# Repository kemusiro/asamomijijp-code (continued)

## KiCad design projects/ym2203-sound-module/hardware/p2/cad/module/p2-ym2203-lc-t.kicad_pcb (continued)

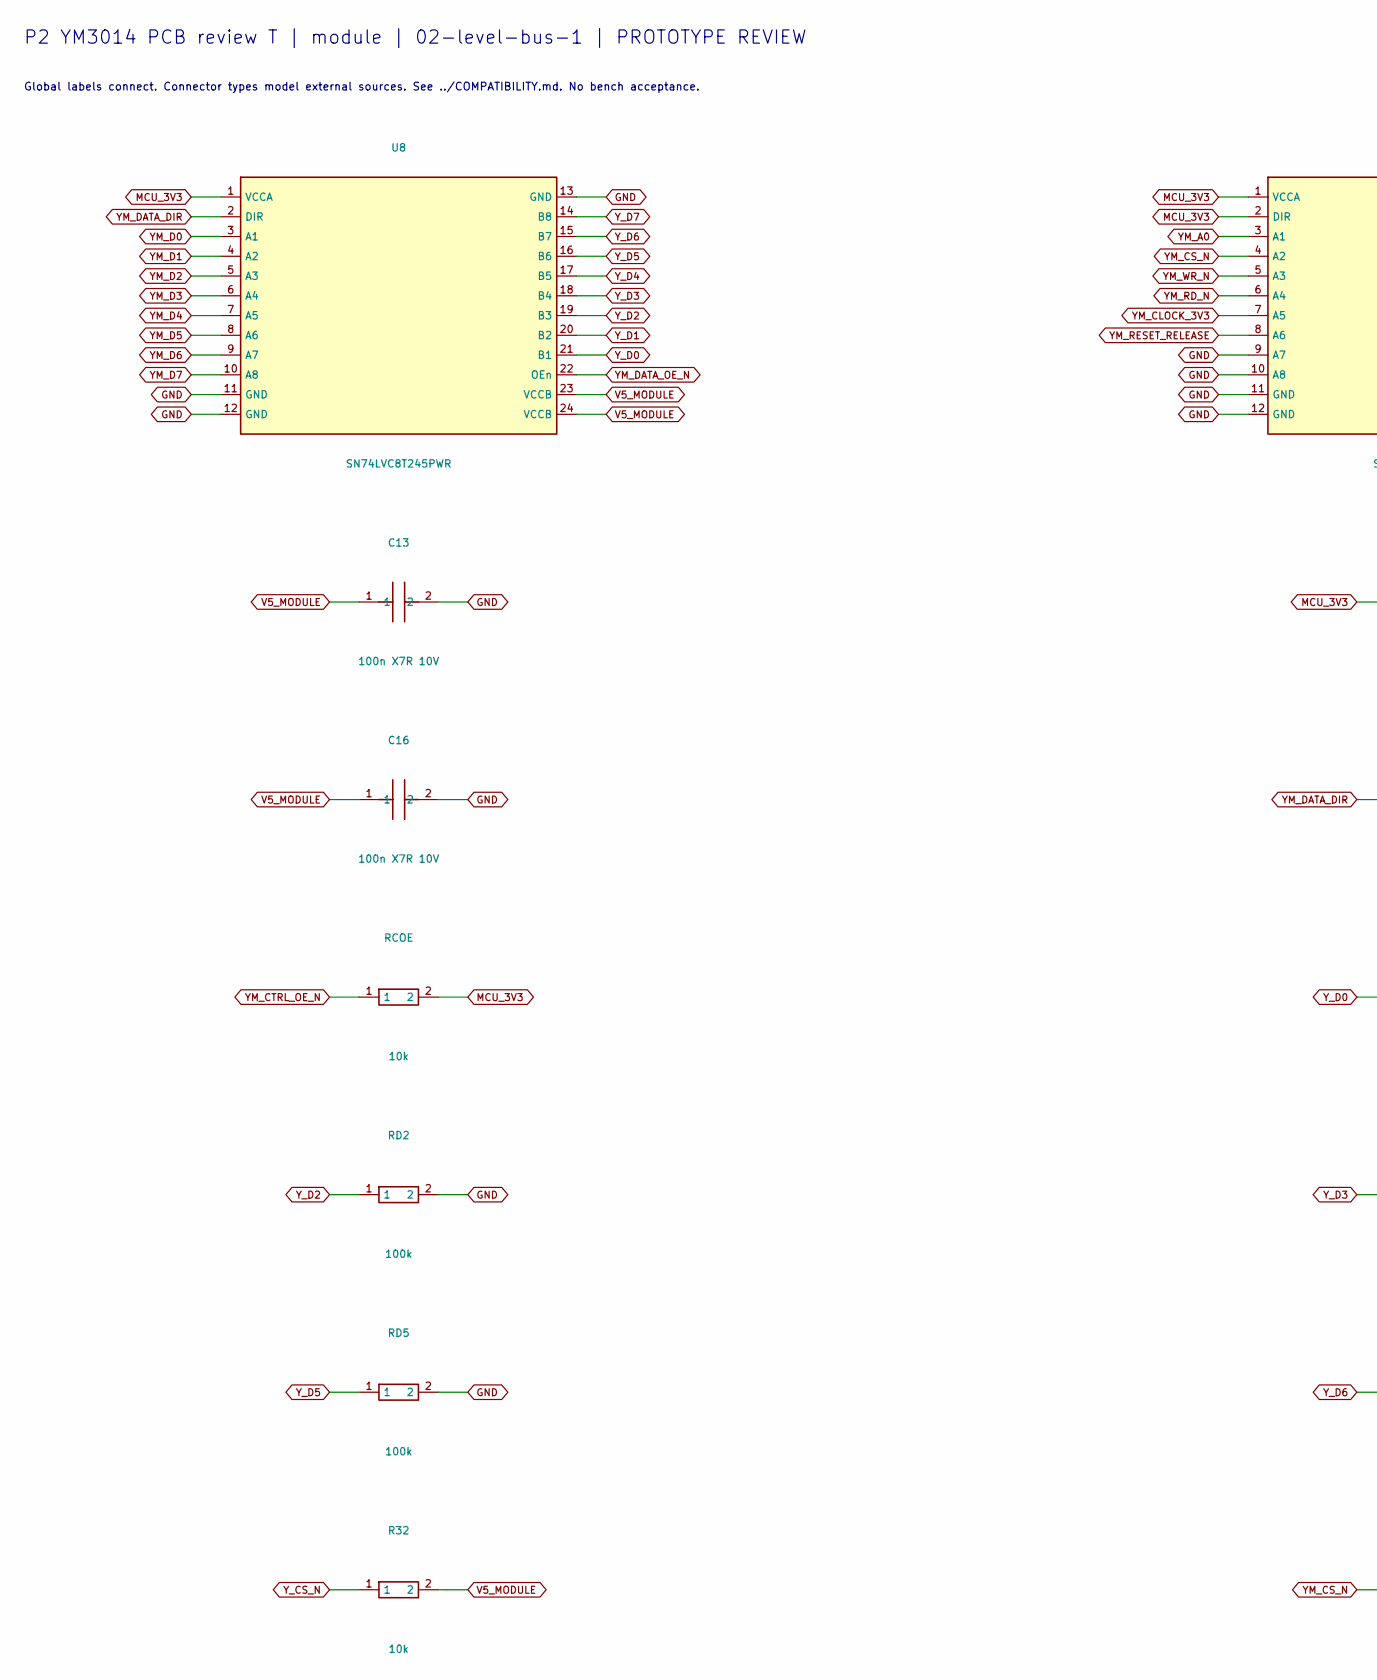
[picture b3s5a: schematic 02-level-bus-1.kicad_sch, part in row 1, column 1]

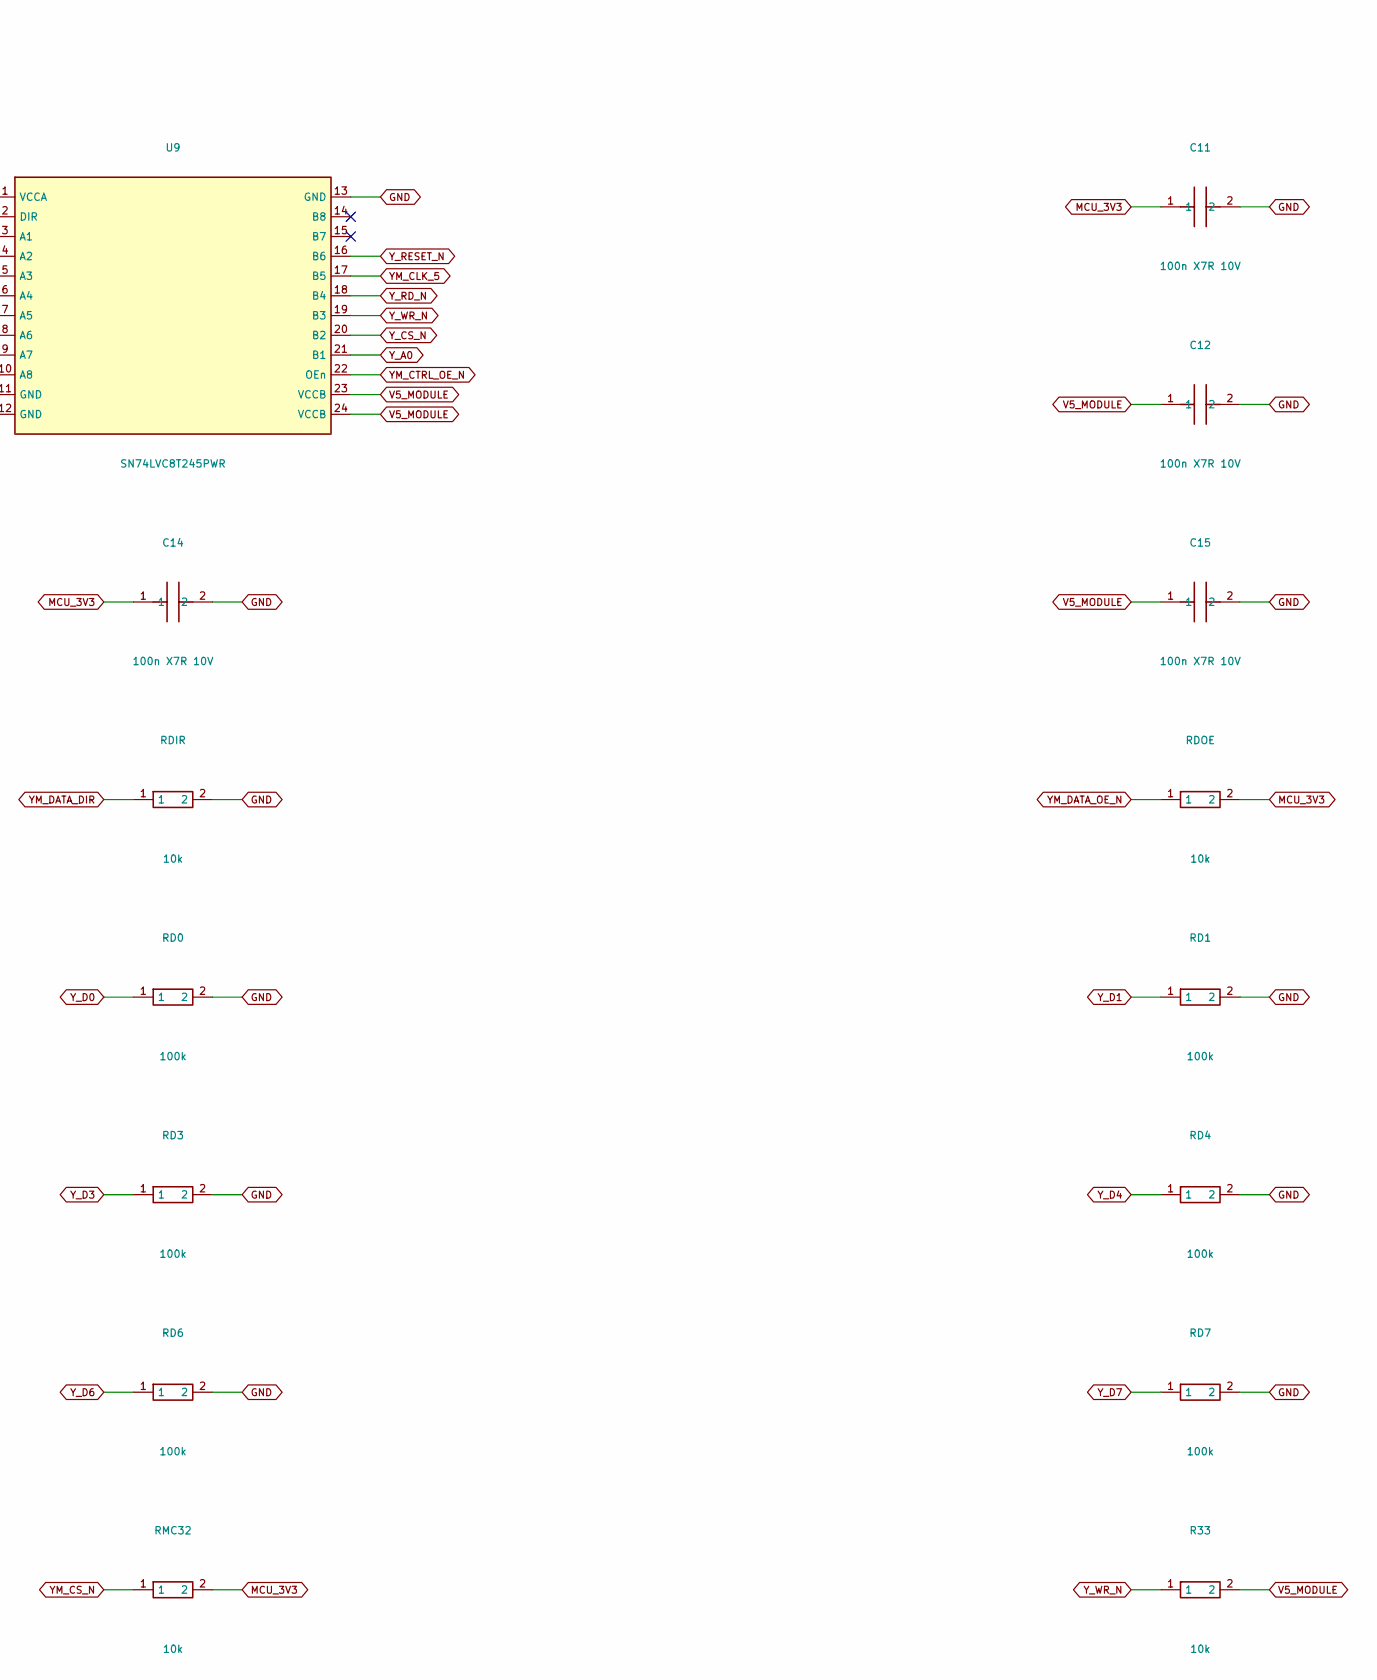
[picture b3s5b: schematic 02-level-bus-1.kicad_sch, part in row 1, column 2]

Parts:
C11, C12, C13, C14, C15, C16: 100n X7R 10V; C_0805_2012Metric
R32, R33: 10k; R_0805_2012Metric
RCOE: 10k; R_0805_2012Metric
RD0, RD1, RD2, RD3, RD4, RD5, RD6, RD7: 100k; R_0805_2012Metric
RDIR: 10k; R_0805_2012Metric
RDOE: 10k; R_0805_2012Metric
RMC32: 10k; R_0805_2012Metric
U8, U9: SN74LVC8T245PWR; TSSOP-24_4.4x7.8mm_P0.65mm

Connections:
GND: C11.2, C12.2, C13.2, C14.2, C15.2, C16.2, RD0.2, RD1.2, RD2.2, RD3.2, RD4.2, RD5.2, RD6.2, RD7.2, RDIR.2, U8.11 (GND), U8.12 (GND), U8.13 (GND), U9.9 (A7), U9.10 (A8), U9.11 (GND), U9.12 (GND), U9.13 (GND); also elsewhere on the board
MCU_3V3: C11.1, C14.1, RCOE.2, RDOE.2, RMC32.2, U8.1 (VCCA), U9.1 (VCCA), U9.2 (DIR); also elsewhere on the board
V5_MODULE: C12.1, C13.1, C15.1, C16.1, R32.2, R33.2, U8.23 (VCCB), U8.24 (VCCB), U9.23 (VCCB), U9.24 (VCCB); also elsewhere on the board
YM_A0: U9.3 (A1); also elsewhere on the board
YM_CLK_5: U9.17 (B5); also elsewhere on the board
YM_CLOCK_3V3: U9.7 (A5); also elsewhere on the board
YM_CS_N: RMC32.1, U9.4 (A2); also elsewhere on the board
YM_CTRL_OE_N: RCOE.1, U9.22 (OEn); also elsewhere on the board
YM_D0: U8.3 (A1); also elsewhere on the board
YM_D1: U8.4 (A2); also elsewhere on the board
YM_D2: U8.5 (A3); also elsewhere on the board
YM_D3: U8.6 (A4); also elsewhere on the board
YM_D4: U8.7 (A5); also elsewhere on the board
YM_D5: U8.8 (A6); also elsewhere on the board
YM_D6: U8.9 (A7); also elsewhere on the board
YM_D7: U8.10 (A8); also elsewhere on the board
YM_DATA_DIR: RDIR.1, U8.2 (DIR); also elsewhere on the board
YM_DATA_OE_N: RDOE.1, U8.22 (OEn); also elsewhere on the board
YM_RD_N: U9.6 (A4); also elsewhere on the board
YM_RESET_RELEASE: U9.8 (A6); also elsewhere on the board
YM_WR_N: U9.5 (A3); also elsewhere on the board
Y_A0: U9.21 (B1); also elsewhere on the board
Y_CS_N: R32.1, U9.20 (B2); also elsewhere on the board
Y_D0: RD0.1, U8.21 (B1); also elsewhere on the board
Y_D1: RD1.1, U8.20 (B2); also elsewhere on the board
Y_D2: RD2.1, U8.19 (B3); also elsewhere on the board
Y_D3: RD3.1, U8.18 (B4); also elsewhere on the board
Y_D4: RD4.1, U8.17 (B5); also elsewhere on the board
Y_D5: RD5.1, U8.16 (B6); also elsewhere on the board
Y_D6: RD6.1, U8.15 (B7); also elsewhere on the board
Y_D7: RD7.1, U8.14 (B8); also elsewhere on the board
Y_RD_N: U9.18 (B4); also elsewhere on the board
Y_RESET_N: U9.16 (B6); also elsewhere on the board
Y_WR_N: R33.1, U9.19 (B3); also elsewhere on the board

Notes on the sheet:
P2 YM3014 PCB review T | module | 02-level-bus-1 | PROTOTYPE REVIEW
Global labels connect. Connector types model external sources. See ../COMPATIBILITY.md. No bench acceptance.

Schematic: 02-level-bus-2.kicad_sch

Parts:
R34: 10k; R_0805_2012Metric
R35: 100k; R_0805_2012Metric
RMA: 100k; R_0805_2012Metric
RMC33, RMC34: 10k; R_0805_2012Metric

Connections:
GND: R35.2, RMA.2; also elsewhere on the board
MCU_3V3: RMC33.2, RMC34.2; also elsewhere on the board
V5_MODULE: R34.2; also elsewhere on the board
YM_A0: RMA.1; also elsewhere on the board
YM_RD_N: RMC34.1; also elsewhere on the board
YM_WR_N: RMC33.1; also elsewhere on the board
Y_A0: R35.1; also elsewhere on the board
Y_RD_N: R34.1; also elsewhere on the board

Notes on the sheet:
P2 YM3014 PCB review T | module | 02-level-bus-2 | PROTOTYPE REVIEW
Global labels connect. Connector types model external sources. See ../COMPATIBILITY.md. No bench acceptance.

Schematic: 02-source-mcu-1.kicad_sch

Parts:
DMCU5V: 1N5819; D_DO-41_SOD81_P10.16mm_Horizontal
JSWD: SWD service / program source 2B; PinHeader_1x03_P2.54mm_Vertical
USOURCE: Picossci 2B RP2350B SSCI-105071; Picossci2B_DirectSolder_DebugWire

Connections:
CORE_RUN_N: USOURCE.SW1.S (RESET_EXTRA_WIRE); also elsewhere on the board
CORE_SWCLK: JSWD.1 (SWCLK), USOURCE.JP1.1 (SWCLK)
CORE_SWD: JSWD.3 (SWDIO), USOURCE.JP1.3 (SWDIO)
FM1_LED_N: USOURCE.J2.2 (GP32); also elsewhere on the board
FM2_LED_N: USOURCE.J2.3 (GP33); also elsewhere on the board
FM3_LED_N: USOURCE.J2.4 (GP34); also elsewhere on the board
GND: JSWD.2 (GND), USOURCE.J2.10 (GND), USOURCE.JP1.2 (GND), USOURCE.JP6.8 (GND), USOURCE.JP7.1 (GND); also elsewhere on the board
LINK_TX_DISABLE: USOURCE.JP7.5 (GP27); also elsewhere on the board
MCU_3V3: USOURCE.J1.1 (3V3_OUT), USOURCE.J2.20 (3V3_OUT); also elsewhere on the board
MCU_5V: DMCU5V.1 (K), USOURCE.J2.19 (REG_IN_5V)
MOD_ALERT_DRIVE: USOURCE.JP6.7 (GP23); also elsewhere on the board
MOD_I2S_BCK: USOURCE.JP7.8 (GP30); also elsewhere on the board
MOD_I2S_DATA: USOURCE.JP7.7 (GP29); also elsewhere on the board
MOD_I2S_LRCK: USOURCE.J2.1 (GP31); also elsewhere on the board
MOD_SPI_CS_N: USOURCE.J1.13 (GP9); also elsewhere on the board
MOD_SPI_MISO: USOURCE.J1.15 (GP11); also elsewhere on the board
MOD_SPI_MOSI: USOURCE.J1.12 (GP8); also elsewhere on the board
MOD_SPI_SCK: USOURCE.J1.14 (GP10); also elsewhere on the board
SSGA_LED_N: USOURCE.J2.5 (GP35); also elsewhere on the board
SSGB_LED_N: USOURCE.J2.6 (GP36); also elsewhere on the board
SSGC_LED_N: USOURCE.J2.7 (GP37); also elsewhere on the board
V5_MODULE: DMCU5V.2 (A); also elsewhere on the board
YM_A0: USOURCE.J1.16 (GP12); also elsewhere on the board
YM_CS_N: USOURCE.J1.17 (GP13); also elsewhere on the board
YM_CTRL_OE_N: USOURCE.JP6.5 (GP21); also elsewhere on the board
YM_D0: USOURCE.J1.4 (GP0); also elsewhere on the board
YM_D1: USOURCE.J1.5 (GP1); also elsewhere on the board
YM_D2: USOURCE.J1.6 (GP2); also elsewhere on the board
YM_D3: USOURCE.J1.7 (GP3); also elsewhere on the board
YM_D4: USOURCE.J1.8 (GP4); also elsewhere on the board
YM_D5: USOURCE.J1.9 (GP5); also elsewhere on the board
YM_D6: USOURCE.J1.10 (GP6); also elsewhere on the board
YM_D7: USOURCE.J1.11 (GP7); also elsewhere on the board
YM_DATA_DIR: USOURCE.JP6.3 (GP19); also elsewhere on the board
YM_DATA_OE_N: USOURCE.JP6.4 (GP20); also elsewhere on the board
YM_FM_CLK: USOURCE.JP6.1 (GP17); also elsewhere on the board
YM_FM_SD: USOURCE.J1.20 (GP16); also elsewhere on the board
YM_FM_SH: USOURCE.JP6.2 (GP18); also elsewhere on the board
YM_RD_N: USOURCE.J1.19 (GP15); also elsewhere on the board
YM_RESET_RELEASE: USOURCE.JP6.6 (GP22); also elsewhere on the board
YM_WR_N: USOURCE.J1.18 (GP14); also elsewhere on the board

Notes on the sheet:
P2 YM3014 PCB review T | module | 02-source-mcu-1 | PROTOTYPE REVIEW
Global labels connect. Connector types model external sources. See ../COMPATIBILITY.md. No bench acceptance.

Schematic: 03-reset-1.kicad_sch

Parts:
CURUNOD: 100n X7R 10V; C_0805_2012Metric
RENPD: 10k; R_0805_2012Metric
RRELDEFAULT: 100k; R_0805_2012Metric
RRUNUP: 10k; R_0805_2012Metric
RYMRESET: 10k; R_0805_2012Metric
URUNOD: SN74LVC1G07DBVR; SOT-23-5

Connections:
CORE_RUN_N: RRUNUP.1, URUNOD.4 (Y); also elsewhere on the board
GND: CURUNOD.2, RENPD.2, RRELDEFAULT.2, RYMRESET.2, URUNOD.3 (GND); also elsewhere on the board
L_MOD_ENABLE: RENPD.1, URUNOD.2 (A); also elsewhere on the board
MCU_3V3: CURUNOD.1, RRUNUP.2, URUNOD.5 (VCC); also elsewhere on the board
YM_RESET_RELEASE: RRELDEFAULT.1; also elsewhere on the board
Y_RESET_N: RYMRESET.1; also elsewhere on the board

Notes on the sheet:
P2 YM3014 PCB review T | module | 03-reset-1 | PROTOTYPE REVIEW
Global labels connect. Connector types model external sources. See ../COMPATIBILITY.md. No bench acceptance.

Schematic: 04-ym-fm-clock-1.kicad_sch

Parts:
C19, C27: 100n X7R 10V; C_0805_2012Metric
C20: 10u 10V; C_0805_2012Metric
CMOD5: 22u X7R 16V C3225X7R1C226K250AC; C_1210_3225Metric
R39: 33; R_0805_2012Metric
R40: 100k; R_0805_2012Metric
RS3, RS6, RS8: 33; R_0805_2012Metric
U12: YM2203C SOCKET; DIP-40_W15.24mm_Socket
U16: SN74LV4T125QPWRQ1; TSSOP-14_4.4x5mm_P0.65mm

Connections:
BUF_M_FM_CLK: RS6.1, U16.6 (Y)
BUF_M_FM_SD: RS3.1, U16.3 (Y)
BUF_M_FM_SH: RS8.1, U16.8 (Y)
GND: C19.2, C20.2, C27.2, CMOD5.2, R40.2, U12.1 (GND), U12.17 (AGND), U16.1 (OEn), U16.4 (OEn), U16.7 (GND), U16.10 (OEn), U16.12 (A); also elsewhere on the board
MCU_3V3: C27.1, U16.13 (OEn), U16.14 (VCC); also elsewhere on the board
SSG_A: U12.20 (SSG_A); also elsewhere on the board
SSG_B: U12.19 (SSG_B); also elsewhere on the board
SSG_C: U12.18 (SSG_C); also elsewhere on the board
V5_MODULE: C19.1, C20.1, CMOD5.1, U12.21 (VDD); also elsewhere on the board
YM_CLK_5: R39.1; also elsewhere on the board
YM_FM_CLK: RS6.2; also elsewhere on the board
YM_FM_SD: RS3.2; also elsewhere on the board
YM_FM_SH: RS8.2; also elsewhere on the board
Y_A0: U12.37 (A0); also elsewhere on the board
Y_CLK: U12.39 (CLK), U16.5 (A); also elsewhere on the board
Y_CS_N: U12.34 (CS_N); also elsewhere on the board
Y_D0: U12.40 (D0); also elsewhere on the board
Y_D1: U12.2 (D1); also elsewhere on the board
Y_D2: U12.3 (D2); also elsewhere on the board
Y_D3: U12.4 (D3); also elsewhere on the board
Y_D4: U12.5 (D4); also elsewhere on the board
Y_D5: U12.6 (D5); also elsewhere on the board
Y_D6: U12.7 (D6); also elsewhere on the board
Y_D7: U12.8 (D7); also elsewhere on the board
Y_PHI_M: R39.2, R40.1, U12.38 (PHI_M)
Y_RD_N: U12.36 (RD_N); also elsewhere on the board
Y_RESET_N: U12.24 (RESET_N); also elsewhere on the board
Y_SD: U12.23 (SD), U16.2 (A); also elsewhere on the board
Y_SH: U12.22 (SH), U16.9 (A); also elsewhere on the board
Y_WR_N: U12.35 (WR_N); also elsewhere on the board

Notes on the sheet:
P2 YM3014 PCB review T | module | 04-ym-fm-clock-1 | PROTOTYPE REVIEW
Global labels connect. Connector types model external sources. See ../COMPATIBILITY.md. No bench acceptance.

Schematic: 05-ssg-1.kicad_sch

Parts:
RL0, RL1, RL2: 1.33k 1%; R_0805_2012Metric
RSMIXA: 10k 1%; R_0805_2012Metric
RSMIXB: 10k 1%; R_0805_2012Metric
RSMIXC: 10k 1%; R_0805_2012Metric

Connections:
AUDIO_R: RSMIXA.2, RSMIXB.2, RSMIXC.2; also elsewhere on the board
GND: RL0.2, RL1.2, RL2.2; also elsewhere on the board
SSG_A: RL0.1, RSMIXA.1; also elsewhere on the board
SSG_B: RL1.1, RSMIXB.1; also elsewhere on the board
SSG_C: RL2.1, RSMIXC.1; also elsewhere on the board

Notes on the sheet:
P2 YM3014 PCB review T | module | 05-ssg-1 | PROTOTYPE REVIEW
Global labels connect. Connector types model external sources. See ../COMPATIBILITY.md. No bench acceptance.

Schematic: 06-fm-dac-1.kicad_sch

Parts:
CANABULK: 10u X7R 10V; C_0805_2012Metric
CFMDAC: 100n X7R 10V; C_0805_2012Metric
COPAMP: 100n X7R 10V; C_0805_2012Metric
CRB: 10u 50V polar; CP_Radial_D5.0mm_P2.00mm
RFMCLK: 33; R_0805_2012Metric
RFMOUT: 100; R_0805_2012Metric
RFMSD: 33; R_0805_2012Metric
RFMSH: 33; R_0805_2012Metric
UAF: MCP6002-E/P; DIP-8_W7.62mm
UDAC: YM3014B-F 16SOP / supplied; YM3014BF_SOP16_5.3x10.2_P1.27mm

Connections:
AUDIO_L: RFMOUT.2; also elsewhere on the board
DAC_CLK: RFMCLK.2, UDAC.10 (CLOCK)
DAC_LOAD: RFMSH.2, UDAC.4 (LOAD)
DAC_MP: UAF.1 (OUT_A), UAF.2 (IN_A-), UDAC.16 (MP)
DAC_RB: CRB.1, UAF.3 (IN_A+), UDAC.14 (RB)
DAC_SD: RFMSD.2, UDAC.7 (SD)
DAC_TO_BUFF: UAF.5 (IN_B+), UDAC.2 (TO_BUFF)
FM_BUF: RFMOUT.1, UAF.6 (IN_B-), UAF.7 (OUT_B)
GND: CANABULK.2, CFMDAC.2, COPAMP.2, CRB.2, UAF.4 (VSS), UDAC.12 (VSS); also elsewhere on the board
V5_MODULE: CANABULK.1, CFMDAC.1, COPAMP.1, UAF.8 (VDD), UDAC.1 (VDD); also elsewhere on the board
Y_CLK: RFMCLK.1; also elsewhere on the board
Y_SD: RFMSD.1; also elsewhere on the board
Y_SH: RFMSH.1; also elsewhere on the board

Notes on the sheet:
P2 YM3014 PCB review T | module | 06-fm-dac-1 | PROTOTYPE REVIEW
Global labels connect. Connector types model external sources. See ../COMPATIBILITY.md. No bench acceptance.

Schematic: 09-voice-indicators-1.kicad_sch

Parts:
DVOICE1: FM1; LED_D3.0mm
DVOICE2: FM2; LED_D3.0mm
DVOICE3: FM3; LED_D3.0mm
DVOICE4: SSGA; LED_D3.0mm
DVOICE5: SSGB; LED_D3.0mm
DVOICE6: SSGC; LED_D3.0mm
RVOICE1, RVOICE2, RVOICE3, RVOICE4, RVOICE5, RVOICE6: 1k; R_0805_2012Metric

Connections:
FM1_LED_N: DVOICE1.1 (K); also elsewhere on the board
FM2_LED_N: DVOICE2.1 (K); also elsewhere on the board
FM3_LED_N: DVOICE3.1 (K); also elsewhere on the board
MCU_3V3: RVOICE1.2, RVOICE2.2, RVOICE3.2, RVOICE4.2, RVOICE5.2, RVOICE6.2; also elsewhere on the board
SSGA_LED_N: DVOICE4.1 (K); also elsewhere on the board
SSGB_LED_N: DVOICE5.1 (K); also elsewhere on the board
SSGC_LED_N: DVOICE6.1 (K); also elsewhere on the board
VOICE_ANODE1: DVOICE1.2 (A), RVOICE1.1
VOICE_ANODE2: DVOICE2.2 (A), RVOICE2.1
VOICE_ANODE3: DVOICE3.2 (A), RVOICE3.1
VOICE_ANODE4: DVOICE4.2 (A), RVOICE4.1
VOICE_ANODE5: DVOICE5.2 (A), RVOICE5.1
VOICE_ANODE6: DVOICE6.2 (A), RVOICE6.1

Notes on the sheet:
P2 YM3014 PCB review T | module | 09-voice-indicators-1 | PROTOTYPE REVIEW
Global labels connect. Connector types model external sources. See ../COMPATIBILITY.md. No bench acceptance.

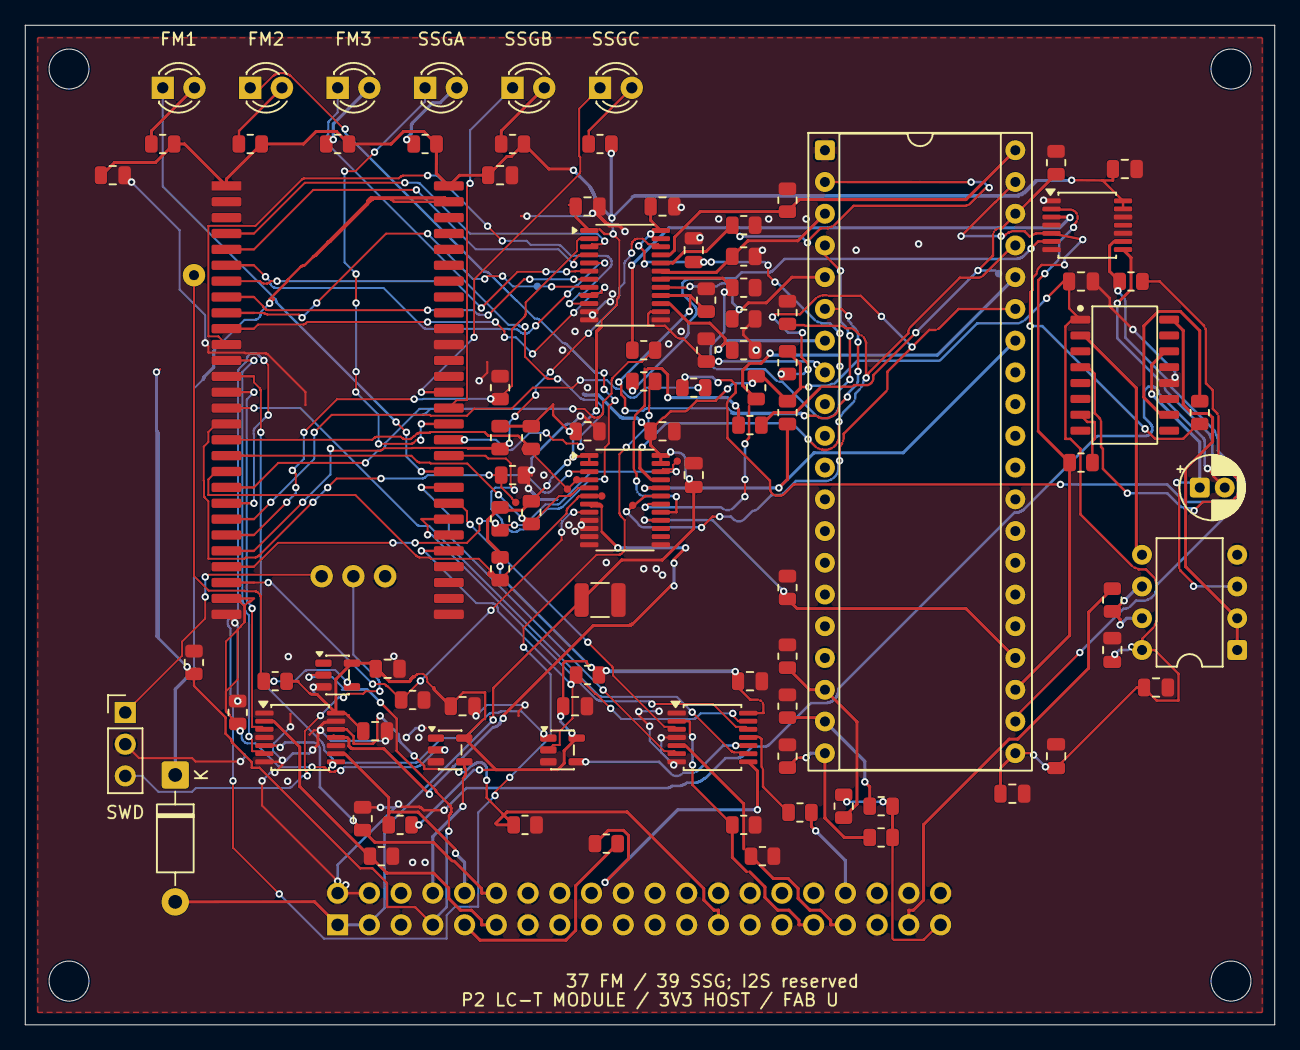
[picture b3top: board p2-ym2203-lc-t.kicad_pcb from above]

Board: 2 copper layers, 100.0 x 80.0 mm, 100 parts (1 on the bottom side), 94 nets.

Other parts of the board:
H1, H2, H3, H4: M3 support
